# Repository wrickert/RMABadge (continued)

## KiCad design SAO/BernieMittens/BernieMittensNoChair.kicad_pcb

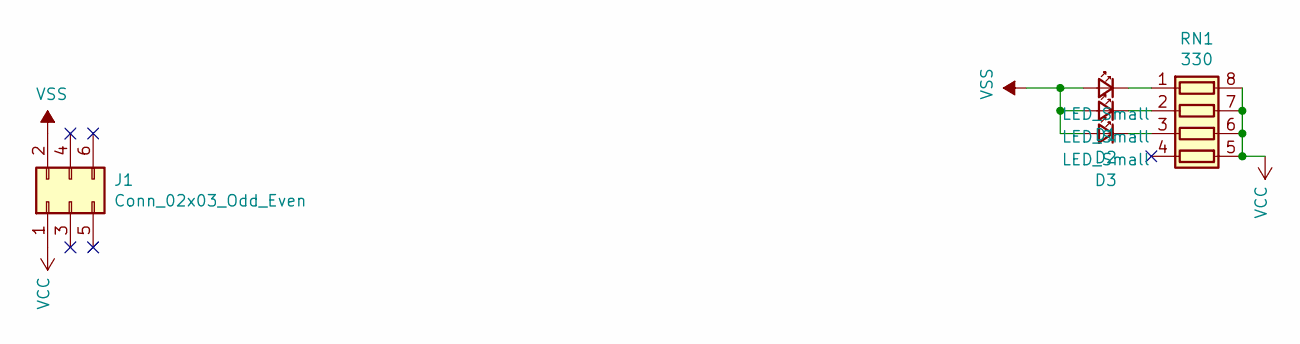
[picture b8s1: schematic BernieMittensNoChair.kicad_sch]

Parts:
D1, D2, D3: LED_Small; RGBFlashLED
J1: Conn_02x03_Odd_Even; PinHeader_2x03_P2.54mm_Vertical_SMD
RN1: 330; R_Array_Convex_4x0603

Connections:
unnamed: D1.1 (K), RN1.1 (R1.1)
unnamed: D2.1 (K), RN1.2 (R2.1)
unnamed: D3.1 (K), RN1.3 (R3.1)
VCC: J1.1, RN1.5 (R4.2), RN1.6 (R3.2), RN1.7 (R2.2), RN1.8 (R1.2)
VSS: D1.2 (A), D2.2 (A), D3.2 (A), J1.2

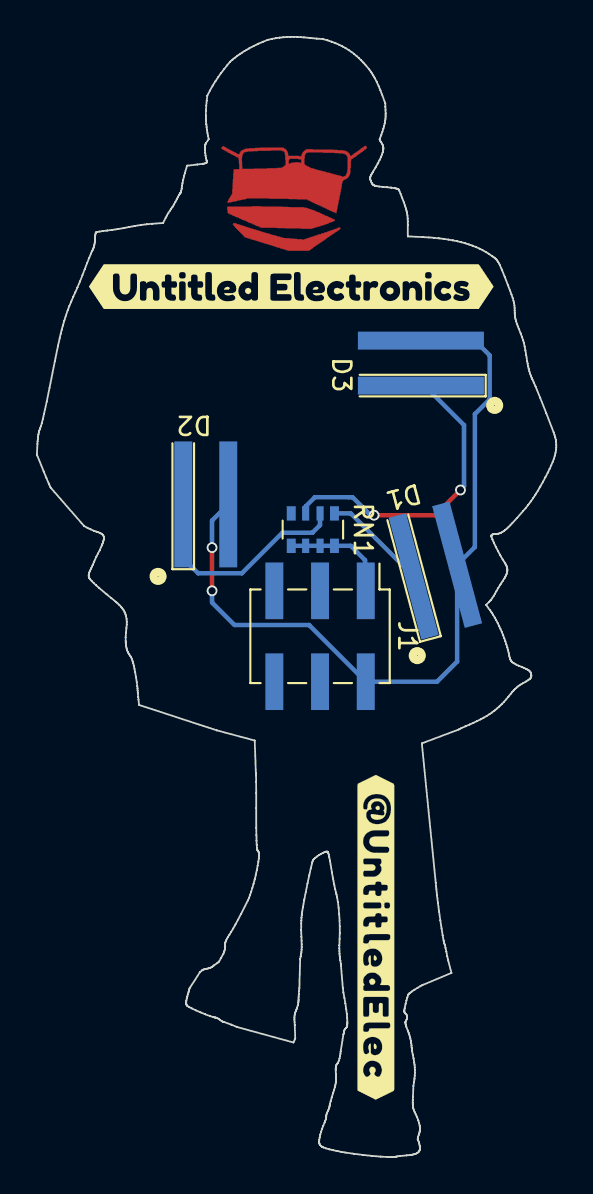
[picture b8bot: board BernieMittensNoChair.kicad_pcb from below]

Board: 2 copper layers, 28.9 x 62.2 mm, 6 parts (6 on the bottom side), 5 nets.

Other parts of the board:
svg2mod: G***; svg2mod

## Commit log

2019-05-06 Inital commit
2019-05-07 Started BreadboardPwr
2019-05-07 Ordered V1 of two different minimal dev boards
2019-05-07 Added switch footprint
2019-05-19 Updated Min dev
2019-06-03 Recieved V1
2019-06-22 Added IS31FL37
2019-07-06 Moving between computers, many changes
2019-07-07 Updates to code
2019-07-19 Making stencils
2019-08-18 Started word clock
2019-08-23 Updates, added schematic pdf
2019-08-27 Firmware
2019-09-02 Progress on Dragos badge
2019-09-11 Almost done
2019-10-04 Added bom
2019-10-09 V2 started
2019-10-10 D Badge V2 ordered
2019-10-25 Firmware in progress
2019-10-27 Firmware progress
2019-10-31 More progress
2019-10-31 Further
2019-11-01 Production V1 firmware and flashing V3 complete
2019-11-01 Okay
2019-11-08 Cleaning up repo
2020-01-06 Added ATGM336H test board
2020-02-15 Finished FJE badge:
2020-02-16 Progress on BSidesIowa badge
2020-02-21 Putting stuff together
2020-03-04 FJE Badge Charlieplexing done
2020-03-07 Progress on FJE firmware
2020-03-07 It works on my machine
2020-03-09 Everything works
2020-03-09 Further progress
2020-03-15 Starte BlueTeamCon
2020-03-26 Started ADV7123 test board
2020-03-28 Started CavemanDAC
2020-06-11 Started USB-C PD project
2020-07-22 Started blue team con cubemx config
2020-07-24 Wrote some test code'
2020-09-06 Updated schematic for new chip
2021-04-11 Some cleanup
2021-04-11 Cleanup, most recent BlueTeamCon badge
2021-04-11 Dualing Devboards V1 complete
2021-04-12 E73 Devboard V1 Complete
2021-05-08 Updates:
2021-05-19 Fixed issue with Blue team con badge
2021-06-05 Blue Team Con V3
2021-06-27 BlueTeamCon firmware in progress
2021-07-12 SAO additions
2021-09-11 Updated for corncon
2021-09-14 Corncon update
2022-02-17 Re-started BsidesIA
2022-03-24 19 to go, please god computer dont die
2022-04-09 Mostly final Corncon
2022-04-24 Finished BSidesIA
2022-06-19 Updates for defcon:
2022-07-02 Updating for picoducky
2023-02-07 Update for hondouras trip
2023-02-26 Added config
2023-03-22 Mostly finished with the T7 totem cad
2026-04-29 cleaning up
